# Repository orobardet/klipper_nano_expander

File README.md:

# Klipper Nano Expander

An Arduino Nano Shield to use with Klipper 3D printer firmware, as a auxiliary MCU.

## Features

- Only require an Arduino Nano
- +5V optional external power supply with fuse
  - Connected to the Arduino Nano 5V
  - Only required if you need more than 500mA power, else the Nano power supply should be enough
- x4 temperature sensors (or any analog device as input)
- x3 PWM mosfet driven port (or any PWM controlled device as output)
- x1 Neopixel (external 5V power supply needed)

- [Schematic](Schematic.pdf)
- [Mechanical drawing](Dimensions.pdf)

Source files:
- Kicad 6 project, schematic, PCB and library
- [CAD files](CAD/), including .STEP and Fusion 360 source

## Why

- Adds more temperature sensors and fan controllers
- Drives 5V fans
- Drives a 5V Neopixel without a level shifter
- Arduino nano are cheap
- Arduino nano are easy to source
- A lot of people (including me) have some in their drawers
- This board only have simple components easy to find
- Small footprint
- Does not need any hardware interaction to flash (no boot jumper or boot button to press)

## How to build

[production directory](production/) contains Gerber file and BOM + Position file for JLCPCB assembly.

If you use JLC PCB to produce and assemble your board, configure PCBA for the bottom side, where most of the SMD
component are placed.  
You'll have to solder by yourself the power indicator LED on the front of the board. It's a 0805, that can be soldered by hand.  
However this LED is not mandatory for the board to work, you can skip soldering it if you want.  
You'll also have to source and solder all the other non-SMD components:
- x2 15 pins female dupont header for the Arduino Nano (or directly the male pin of the Nano, which is not recommended)
- x1 [Keystone 3544-2 mini fuse holder](https://www.digikey.com/en/products/detail/keystone-electronics/3544-2/316029)
- x7 2 pins JST connector (FANx and THx headers)
- x1 3 pins JST connector (Neopixel headers)
- x1 screw terminal pitch 5.08mm for power in

### BOM

- [Interactive BOM](http://htmlpreview.github.io/?https://github.com/orobardet/klipper_nano_expander/blob/master/interactive_bom/klipper_nano_expander_interactive_bom.html)
- [CSV](Klipper_nano_expander-BOM.csv) or [XLSX](Klipper_nano_expander-BOM.xlsx) BOM

Ref                | Qty | Value          | Description                                              | Soldering     | Footprint         | LCSC Ref
-------------------|-----|----------------|----------------------------------------------------------|---------------|-------------------|------------
C1, C8             |   2 | 10uF	          | Unpolarized ceramic capacitor                            | PCBA          | 0805              | [C17024](https://lcsc.com/product-detail/Multilayer-Ceramic-Capacitors-MLCC-SMD-SMT_Samsung-Electro-Mechanics-CL21A106KPFNNNE_C17024.html)
C2, C3             |   2 | 0.1uF          | Unpolarized ceramic capacitor                            | PCBA          | 0805              | [C49678](https://lcsc.com/product-detail/Multilayer-Ceramic-Capacitors-MLCC-SMD-SMT_YAGEO-CC0805KRX7R9BB104_C49678.html)
C4, C5, C6, C7     |   4 | 4.7uF          | Unpolarized ceramic capacitor                            | PCBA          | 0805              | [C1779](https://lcsc.com/product-detail/Multilayer-Ceramic-Capacitors-MLCC-SMD-SMT_Samsung-Electro-Mechanics-CL21A475KAQNNNE_C1779.html)
Q1, Q2, Q3         |   3 | IRLML6344TRPBF | MOSFET N-CH 30V 5A SOT23                                 | PCBA          | SOT-23            | [C20917](https://lcsc.com/product-detail/MOSFETs_Alpha-Omega-Semicon-AO3400A_C20917.html)
R1                 |   1 | 1K             | Resistor                                                 | PCBA          | 0805              | [C17513](https://lcsc.com/product-detail/Chip-Resistor-Surface-Mount_UNI-ROYAL-Uniroyal-Elec-0805W8F1001T5E_C17513.html)
R3, R6, R9, R15    |   4 | 100            | Resistor                                                 | PCBA          | 0805              | [C17408](https://lcsc.com/product-detail/Chip-Resistor-Surface-Mount_UNI-ROYAL-Uniroyal-Elec-0805W8F1000T5E_C17408.html)
R4, R7, R10        |   3 | 10K            | Resistor                                                 | PCBA          | 0805              | [C17414](https://lcsc.com/product-detail/Chip-Resistor-Surface-Mount_UNI-ROYAL-Uniroyal-Elec-0805W8F1002T5E_C17414.html)
R11, R12, R13, R14 |   4 | 4.7K           | Resistor                                                 | PCBA          | 0805              | [C17673](https://lcsc.com/product-detail/Chip-Resistor-Surface-Mount_UNI-ROYAL-Uniroyal-Elec-0805W8F4701T5E_C17673.html)
D3                 |   1 | Any color      | LED                                                      | PCBA          | 0805              | [C84256](https://lcsc.com/product-detail/Light-Emitting-Diodes-LED_Foshan-NationStar-Optoelectronics-NCD0805R1_C84256.html)
A1                 |   1 |                | Arduino Nano v3.x                                        | Hand-soldered |                   |
A1-a, A1-b         |   2 |                | 15 pins female dupont header + 15 mins mal dupont header | Hand-soldered | P2.54             |
F1                 |   1 | Fuse           | Mini fuse holder + 2A or 5A mini fuse                    | Hand-soldered | 3544-2_FuseHolder | 	
J1                 |   1 |                | Screw terminal 2 pins P5.08mm                            | Hand-soldered | P5.08mm           | 
FAN0, FAN1, FAN2   |   3 |                | JST 2 pins P2.54mm                                       | Hand-soldered | P2.54             | 
T0, T1, T2, T3     |   4 |                | JST 2 pins P2.54mm                                       | Hand-soldered | P2.54             | 
Neopixel           |   1 |                | JST 3 pins P2.54mm                                       | Hand-soldered | P2.54             | 

## How to use

**ONLY** use **5V** power supply! The Vin of the bord is connected to the 5V of the Arduino Nano, with no protection:  
any power >5V may fry your Nano, and any power <5V may fry you power supply.

Powering on Vin with an external 5V power supply is only necessary if you device draw more current than the Nano can provide (800mA theorically, 
but with so many Nano clone out there it's safer to stick to 500mA max).
- If you only plug temperature sensors, the Nano power supply should be enough
- If you drive a fan, I'd better power the board with external power supply (most fan draws more then 500mA when they start)
- If you drive an neopixel, **powering the board with external power supply is highly recommended**

In doubt, power the board. You should already have a 5V power source if you use Klipper, to power the Pi.

FANx header are mosfet PWM output, driving the ground:
- You can use them for anything else than FAN, like LED, heater, etc. Just stick to 1A per output max.
- If the fan or whatever you drive is not 5V, just connect its ground to the Klipper Nano Expander, and its +V to any compatible power source, **but ensure that other PSU's ground is connected to the board ground!**.

### Software configuration

Once built and connected to your Klipper host, use the provided [Klipper config file](config/nano_klipper_expander.cfg).  

You need at least to set the `serial` path in the `[mcu ...]` of the provided klipper configuration file.  
To find the serial of your Arduino Nano:
- BEFORE connecting the Nano with USB on the Raspberry Pi, connect to the Pi using SSH and run the command `ls /dev/serial/by-id/`. Note the result.
- Connect the Nano with USB on the Pi, wait a few seconds for the Pi to detect the USB device, and re-run the same command as before.
- A new "file" should be there, looking like `usb-1a86_USB2.0-Serial-if00-port0`: it represents your Arduino Nano
- Change the `serial` setting value in the Klipper configuration using the full path to the serial file. e.g.: `serial: /dev/serial/by-id/usb-1a86_USB2.0-Serial-if00-port0`

Here is the pin mapping for reference:
- TH0: PC0
- TH1: PC1
- TH2: PC2
- TH3: PC3
- FAN0: PB1
- FAN1: PD5
- FAN2: PD3
- Neopixel Data: PD6

The configuration file must be included in some way into the main `printer.cfg` config filr of Klipper.

### Flashing firmware

To flash the firmware, you do not need to have the configuration file ready, but you need:
- The Nano connected to the Raspberry Pi
- The path of the serial representing the Nano on the Pi (see previous section)
- Klipper installed on the Pi
- AVR compilation package installed on the Rapsberry Pi hosting Klipper: `sudo apt install gcc-avr avr-libc avrdude binutils-avr`

To flash the Nano with Klipper:

- Connect to the Pi using SSH.
- Create a `klipper_config` directory in you home directory, if it not exists already: `mkdir -p ~/klipper_config`.
- Go the the directory containing klipper (usually: `cd ~/klipper`).
- Run `make clean KCONFIG_CONFIG=~/klipper_config/config.arduinonano`.
- Run `make menuconfig KCONFIG_CONFIG=~/klipper_config/config.arduinonano` and configure as followed, and then save'n'quit:  
  - _Enable extra low-level configuration options_: NOT checked
  - _Micro-controller Architecture_: `Atmega AVR`
  - _Processor model_: `atmega328p`   

- Run `make KCONFIG_CONFIG=~/klipper_config/config.arduinonano` to build the firmware.  
  **Note:** If the firmware compilation fails with errors like `'.data' is not within region 'data'`, you may sufffer a known bug with AVR toolchain on Debian Bullseye (check your linux distribution codename with `lsb_release -a`). If so, you can try [a workaround describe here to install a previous and non-buggy AVR toolchain](https://github.com/Klipper3d/klipper/issues/4938#issuecomment-1094246978). Once installed, re-roll the current procedure from the `make clean` step (a reboot of the Pi may be usefull between new toolchain installation and the retry).
- **Stop Klipper** if it's running (usually: `sudo systemctl stop klipper`)
- Run `make flash KCONFIG_CONFIG=~/klipper_config/config.arduinonano FLASH_DEVICE=/dev/serial/by-id/usb-1a86_USB2.0-Serial-if00-port0`, _**replacing the `FLASH_DEVICE=` value with the full path of you Nano on your Pi!**_ This will flash the firmware to the Arduino Nano.
- Start Klipper (usually: `sudo systemctl start klipper`)

If no error occurs, Klipper's firmware is now loaded into the Arduino Nano.  
You can now configure Klipper to use the Nano Expander.

### Mounting

x2 3D printable mounts are provided (STL files):
- [without mounting holes](STL/nano_expander_mount.stl): lower footprint, but require some tape (like VHB tape) to secure the mount on a flat surface.
- [with mounting holes](STL/nano_expander_mount_with_holes.stl): a wider mount with 4 mounting holes, to secure the mount with M3 screws. Screws position and distance can be found in [dimension drawing](Dimensions.pdf).

Both mounts require x4 M2x3mm screw to secure the board to the mount.

## Compatibility

Aside from Arduino Nano and its clone, this board _may_ be compatible with other MCU boards using the same form factor than the Arduino Nano, and a compatible pinout.

- [Cytron Maker Nano RP2040](config/rp2040_klipper_expander.cfg): flashing the firmware is a bit different, as it is based on the Raspberry Pi RP2040 MCU rather than an ATMega MCU. 

## Credit

Inspired by [STM32-Klipper-Expander](https://github.com/VoronDesign/Voron-Hardware/tree/master/Klipper_Expander) by Voron Design Team.  
Temperature sensors and FAN output of Klipper Nano Expander are a copy of those of STM32-Klipper-Expander.  
The Cytron Maker Nano RP2040 config is a contribution of **tehmaze** (#2).

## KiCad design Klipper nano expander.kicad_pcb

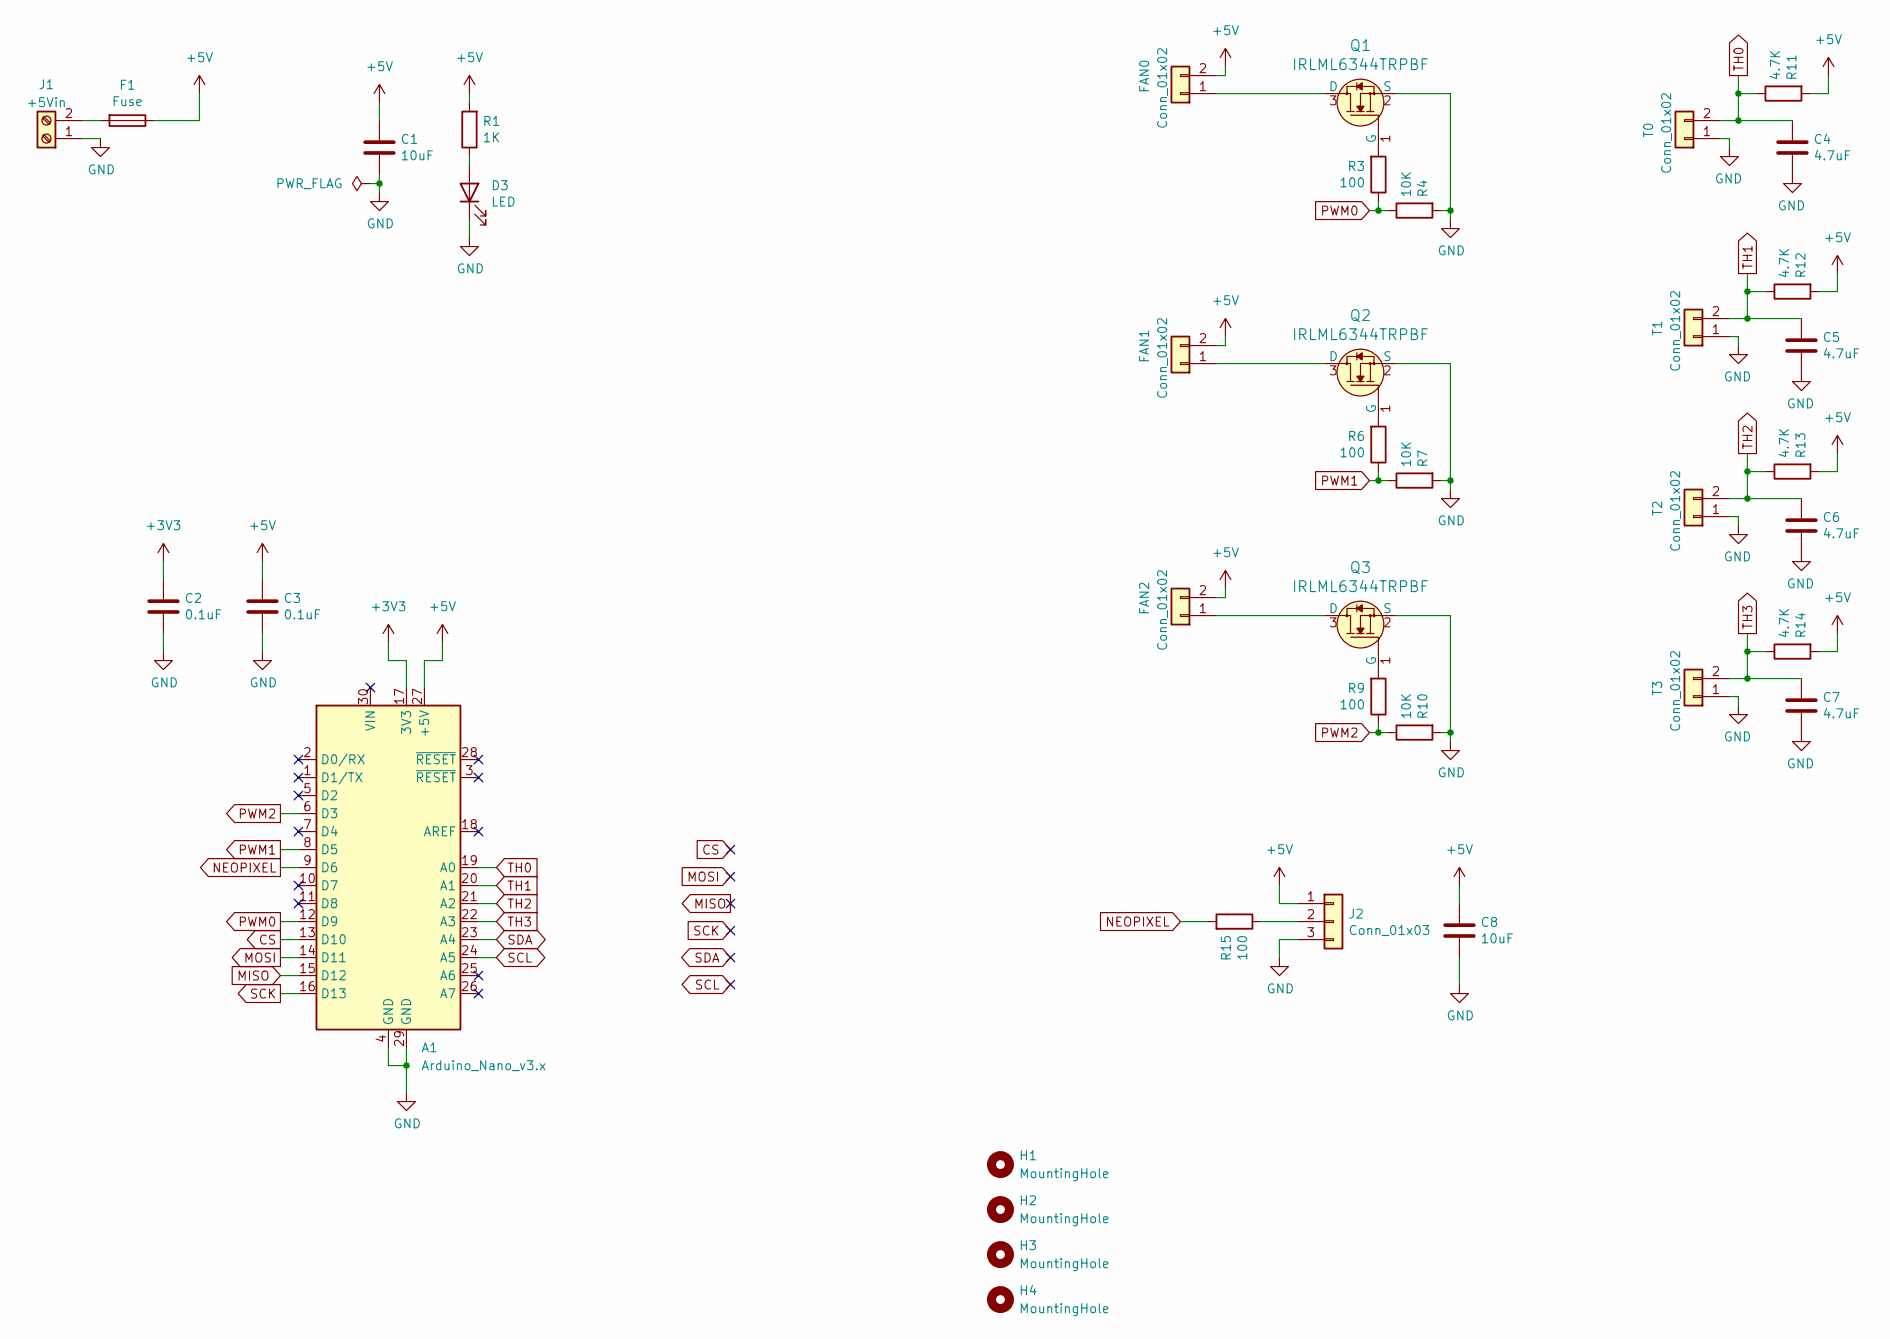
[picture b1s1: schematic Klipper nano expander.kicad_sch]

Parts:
A1: Arduino_Nano_v3.x; Arduino_Nano_WithMountingHoles
C1, C8: 10uF; C_0805_2012Metric; MPN CL21A106KPFNNNE; LCSC C17024
C2, C3: 0.1uF; C_0805_2012Metric; MPN CC0805KRX7R9BB104; LCSC C49678
C4, C5, C6, C7: 4.7uF; C_0805_2012Metric; MPN CC0805KKX5R8BB475; LCSC C1779
D3: LED; LED_0805_2012Metric; MPN 17-215SURC/S530-A2/TR8; LCSC C84256
F1: Fuse; 3544-2_FuseHolder
FAN0, FAN1, FAN2: Conn_01x02; JST_XH_B2B-XH-A_1x02_P2.50mm_Vertical
H1, H2, H3, H4: MountingHole; MountingHole_2mm
J1: +5Vin; TerminalBlock_Phoenix_MKDS-1,5-2-5.08_1x02_P5.08mm_Horizont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
J2: Conn_01x03; JST_XH_B3B-XH-A_1x03_P2.50mm_Vertical
Q1, Q2, Q3: IRLML6344TRPBF; SOT-23; MPN IRLML6344TRPBF; Digi-Key_PN IRLML6344TRPBFCT-ND
R1: 1K; R_0805_2012Metric; MPN RC0805JR-071KL; LCSC C17513
R3, R6, R9, R15: 100; R_0805_2012Metric; MPN RC0805JR-07100RL; LCSC C17408
R4, R7, R10: 10K; R_0805_2012Metric; MPN RC0805JR-0710KL; LCSC C17414
R11, R12, R13, R14: 4.7K; R_0805_2012Metric; MPN RC0805JR-074K7L; LCSC C17673
T0, T1, T2, T3: Conn_01x02; JST_XH_B2B-XH-A_1x02_P2.50mm_Vertical

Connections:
+3V3: A1.17 (3V3), C2.2
+5V: A1.27 (+5V), C1.2, C3.2, C8.2, F1.1, FAN0.2, FAN1.2, FAN2.2, J2.1, R1.2, R11.2, R12.2, R13.2, R14.2
CS: A1.13 (D10)
GND: A1.4 (GND), A1.29 (GND), C1.1, C2.1, C3.1, C4.1, C5.1, C6.1, C7.1, C8.1, D3.1 (K), J1.1, J2.3, Q1.2 (S), Q2.2 (S), Q3.2 (S), R4.2, R7.2, R10.2, T0.1, T1.1, T2.1, T3.1
MISO: A1.15 (D12)
MOSI: A1.14 (D11)
NEOPIXEL: A1.9 (D6), R15.2
unnamed: D3.2 (A), R1.1
unnamed: F1.2, J1.2
unnamed: FAN0.1, Q1.3 (D)
unnamed: FAN1.1, Q2.3 (D)
unnamed: FAN2.1, Q3.3 (D)
unnamed: J2.2, R15.1
unnamed: Q1.1 (G), R3.2
unnamed: Q2.1 (G), R6.2
unnamed: Q3.1 (G), R9.2
PWM0: A1.12 (D9), R3.1, R4.1
PWM1: A1.8 (D5), R6.1, R7.1
PWM2: A1.6 (D3), R9.1, R10.1
SCK: A1.16 (D13)
SCL: A1.24 (A5)
SDA: A1.23 (A4)
TH0: A1.19 (A0), C4.2, R11.1, T0.2
TH1: A1.20 (A1), C5.2, R12.1, T1.2
TH2: A1.21 (A2), C6.2, R13.1, T2.2
TH3: A1.22 (A3), C7.2, R14.1, T3.2

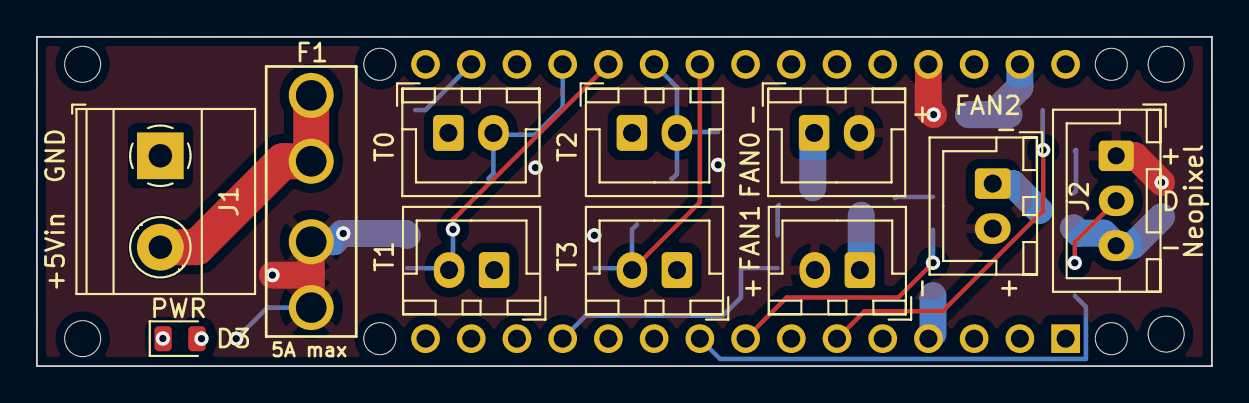
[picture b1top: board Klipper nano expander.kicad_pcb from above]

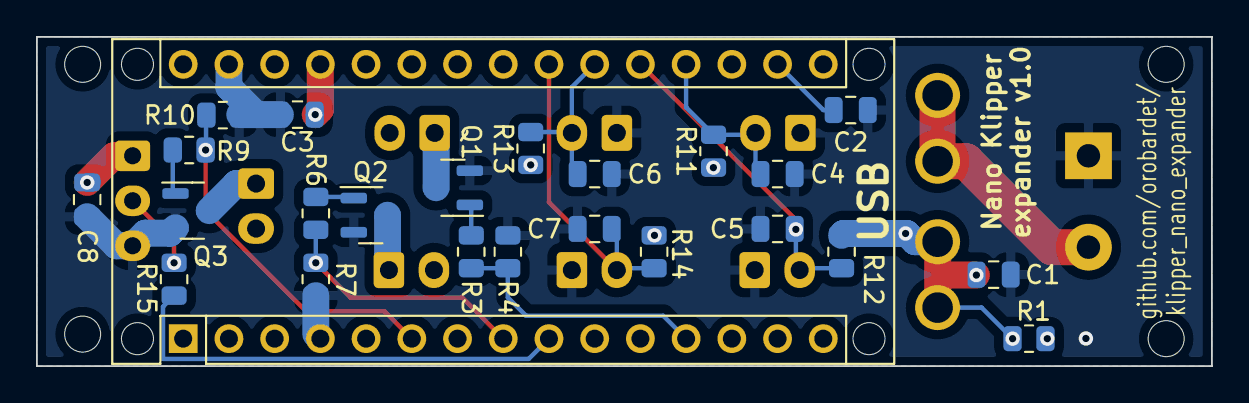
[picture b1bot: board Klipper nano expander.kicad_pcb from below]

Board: 2 copper layers, 65.3 x 18.3 mm, 39 parts (24 on the bottom side), 20 nets.

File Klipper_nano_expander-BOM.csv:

Ref;Qty;Value;Description;Footprint;LCSC Ref
A1;1;;Arduino Nano v3.x;;
A1-a, A1-b;2;;15 pins female dupont header + 15 mins mal dupont header;;
C1, C8;2;10uF;Unpolarized ceramic capacitor;0805;C17024
C2, C3;2;0.1uF;Unpolarized ceramic capacitor;0805;C49678
C4, C5, C6, C7;4;4.7uF;Unpolarized ceramic capacitor;0805;C1779
D3;1;Any color;LED;0805;C84256
F1;1;Fuse;Mini fuse holder + 2A or 5A mini fuse;3544-2_FuseHolder;
Q1, Q2, Q3;3;IRLML6344TRPBF;MOSFET N-CH 30V 5A SOT23;SOT-23;C20917
R1;1;1K;Resistor;0805;C17513
R3, R6, R9, R15;4;100;Resistor;0805;C17408
R4, R7, R10;3;10K;Resistor;0805;C17414
R11, R12, R13, R14;4;4.7K;Resistor;0805;C17673
J1;1;;Screw terminal 2 pins P5.08mm;P5.08mm;
FAN0, FAN1, FAN2;3;;JST 2 pins P2.54mm;P2.54;
T0, T1, T2, T3;4;;JST 2 pins P2.54mm;P2.54;
Neopixel;1;;JST 3 pins P2.54mm;P2.54;

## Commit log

2022-06-19 Fix interactive BOM link
2022-07-05 Fix screw terminal pitch in description
    And some type
2022-11-11 Add flashing firmware instructions
2023-04-11 Create rp2040_klipper_expander.cfg
    Reference configuration for the Cytron Maker Nano RP2040, for those looking to use a Pi Pico (rev B2) RP2040 micro controller, rather than the Arduino ATMega series.
2023-04-12 Add alternative MCU boards and Cytron Maker Nano RP2040
